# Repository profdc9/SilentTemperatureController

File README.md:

# Silent Temperature Controller

This is a heating temperature controller intended to minimize the vibrations caused by the heating element.  It uses kHz speed PWM modulated DC, rather than switching 50 or 60 cycle mains power, to power the heating elements.  For explosing holographic emulsions, the temperature must be stable and the vibrations must be minimized so that the sub-wavelength interference features are preserved.  By using high frequency PWM, the mechanical vibration or magnetostriction of the heating element coils is raised above a likely resonance frequency and therefore unlikely to cause significant vibrational movement.

The temperature controller can use up to three B3950 10k nominal resistance thermistors, or alternatively a LM335 temperature-based zener diode.  Reference thermistors may be added so that differential measurements can be taken to compensate for component temperature drift.  The controller supports up to four heating elements.  The DC power supply is up to 24 volts and 10 amps or so, with the limitation given by the trace width on the PCB.  If additional power bus wires are soldered in parallel with the traces, a higher current capacity is likely possible.  It is best to place the thermistors and heating elements in a vibration isolated, thermally insulated enclosure in which the hologram is exposed, with the enclosure being small enough so that the heaters can maintain a constant temperature throughout the volume.  A vibration-isolated platform may be achieved by placing a heavy cement slab or granite slab on partially inflated tires, and the granite slab may be made part of a thermally insulated enclosure using polystryrene slabs as walls.

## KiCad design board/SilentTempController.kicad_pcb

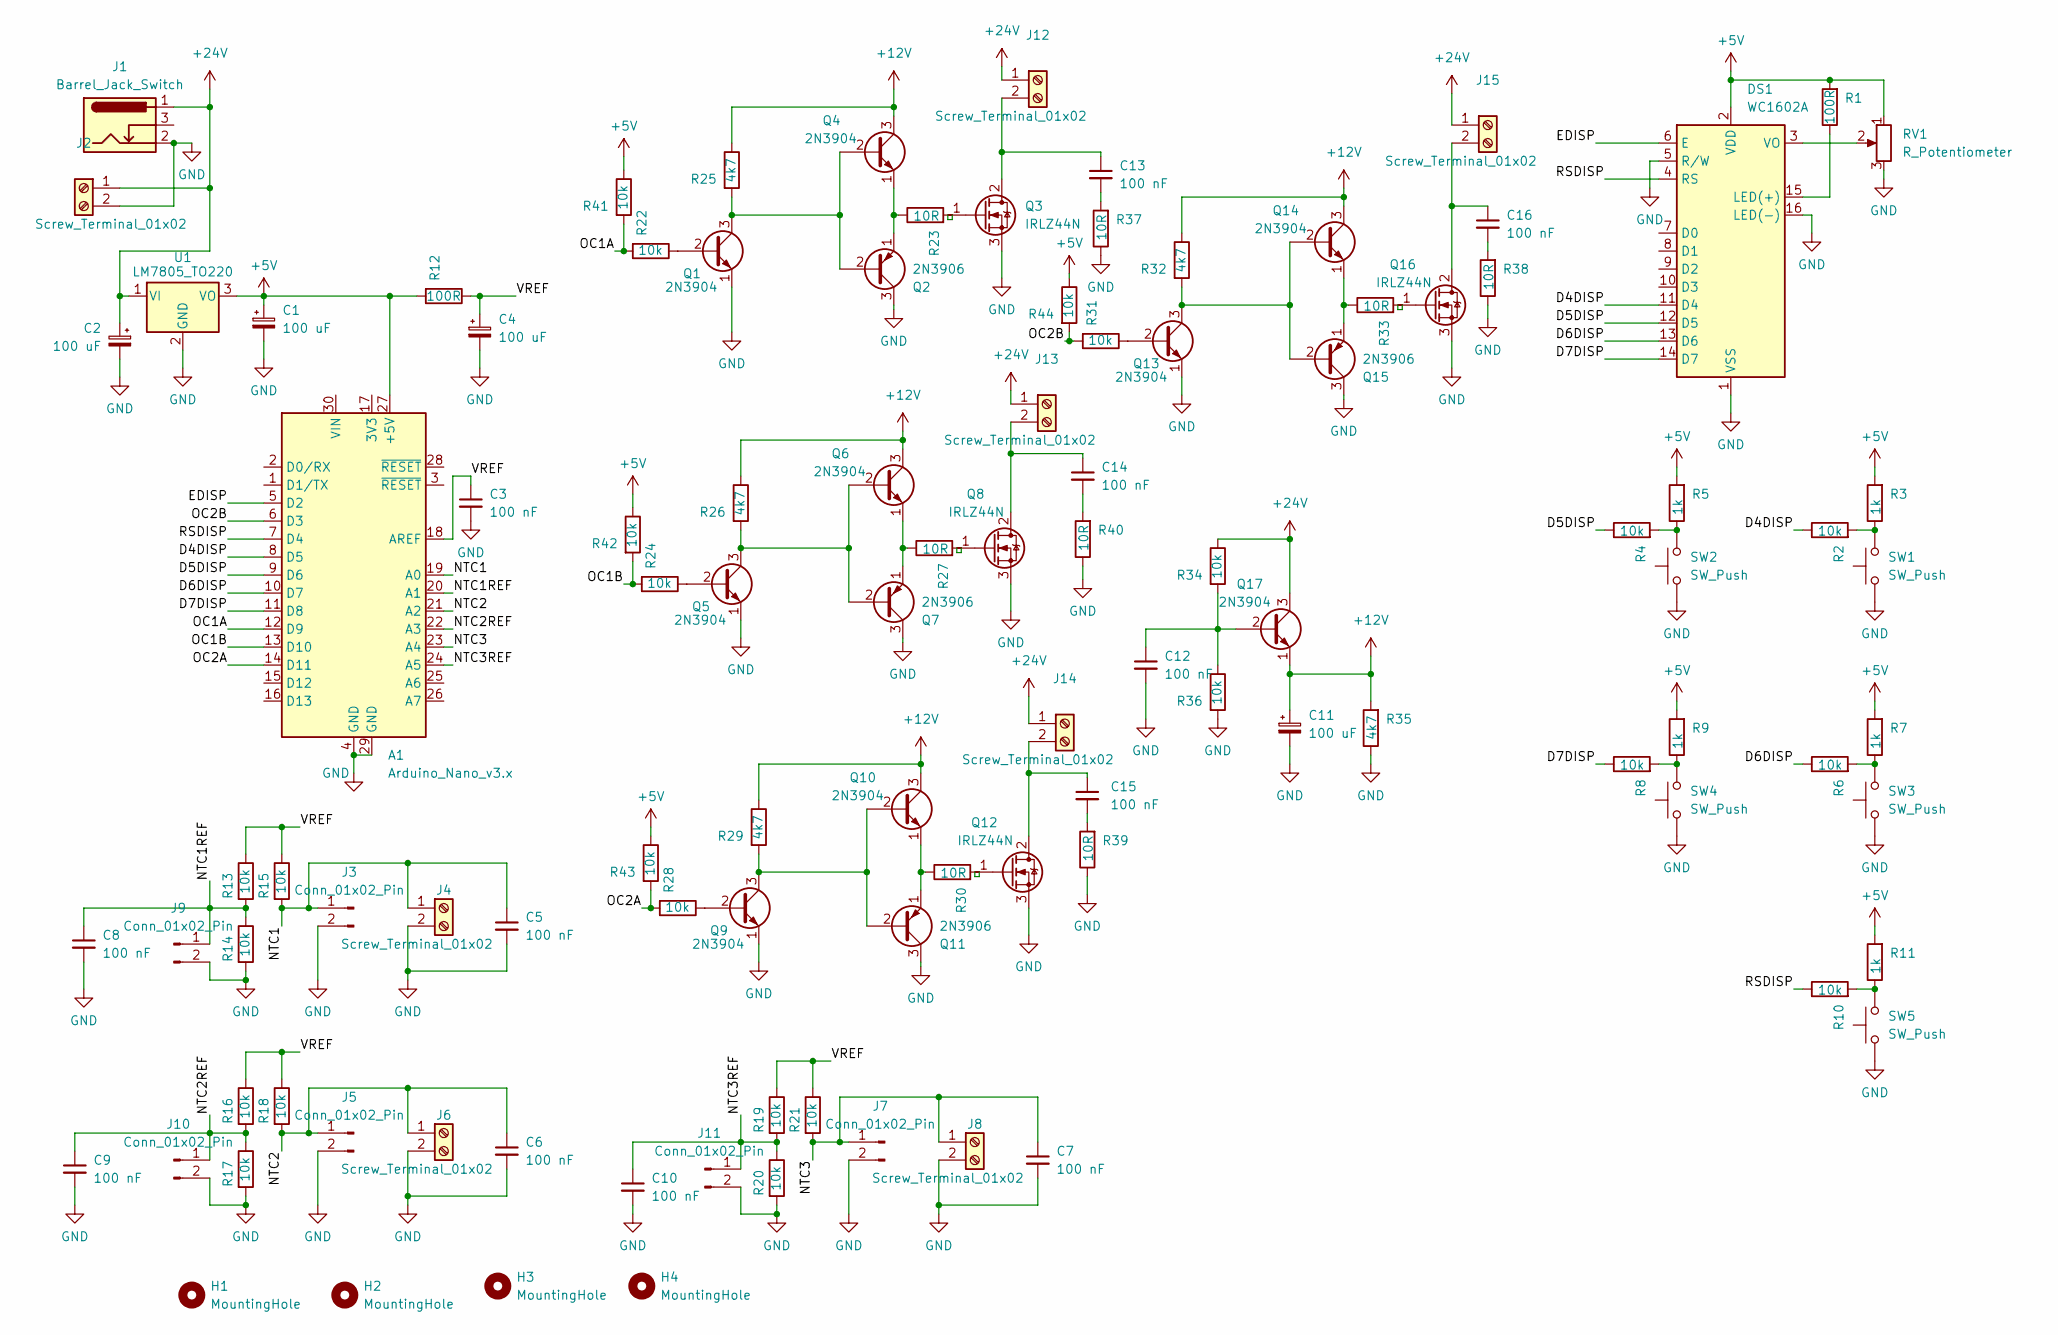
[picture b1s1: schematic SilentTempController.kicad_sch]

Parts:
A1: Arduino_Nano_v3.x; Arduino_Nano
C1, C2, C4, C11: 100 uF; CP_Radial_D7.5mm_P2.50mm
C3, C5, C6, C7, C8, C9, C10, C12, C13, C14, C15, C16: 100 nF; C_Disc_D5.0mm_W2.5mm_P5.00mm
DS1: WC1602A
H1, H2, H3, H4: MountingHole; MountingHole_3.2mm_M3
J1: Barrel_Jack_Switch; BarrelJack_Horizontal
J2, J4, J6, J8, J12, J13, J14, J15: Screw_Terminal_01x02; TerminalBlock_bornier-2_P5.08mm
J3, J5, J7, J9, J10, J11: Conn_01x02_Pin; PinHeader_1x02_P2.54mm_Vertical
Q1, Q4, Q5, Q6, Q9, Q10, Q13, Q14, Q17: 2N3904; TO-92_Inline_Wide
Q2, Q7, Q11, Q15: 2N3906; TO-92_Inline_Wide
Q3, Q8, Q12, Q16: IRLZ44N; TO-220-3_Vertical
R1, R12: 100R; R_Axial_DIN0207_L6.3mm_D2.5mm_P7.62mm_Horizontal
R2, R4, R6, R8, R10, R13, R14, R15, R16, R17, R18, R19, R20, R21, R22, R24, R28, R31, R34, R36, R41, R42, R43, R44: 10k; R_Axial_DIN0207_L6.3mm_D2.5mm_P7.62mm_Horizontal
R3, R5, R7, R9, R11: 1k; R_Axial_DIN0207_L6.3mm_D2.5mm_P7.62mm_Horizontal
R23, R27, R30, R37, R38, R39, R40: 10R; R_Axial_DIN0207_L6.3mm_D2.5mm_P7.62mm_Horizontal
R25, R26, R29, R32, R35: 4k7; R_Axial_DIN0207_L6.3mm_D2.5mm_P7.62mm_Horizontal
R33: 10R; R_Axial_DIN0207_L6.3mm_D2.5mm_P10.16mm_Horizontal
RV1: R_Potentiometer; Potentiometer_Bourns_3296W_Vertical
SW1, SW2, SW3, SW4, SW5: SW_Push; SW_PUSH_6mm
U1: LM7805_TO220; TO-220-3_Vertical

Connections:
+5V: A1.27 (+5V), C1.1, DS1.2 (VDD), R1.2, R3.2, R5.2, R7.2, R9.2, R11.2, R12.2, R41.1, R42.1, R43.1, R44.1, RV1.1, U1.3 (VO)
+12V: C11.1, Q4.3 (C), Q6.3 (C), Q10.3 (C), Q14.3 (C), Q17.1 (E), R25.1, R26.1, R29.1, R32.1, R35.2
+24V: C2.1, J1.1, J2.1, J12.1, J13.1, J14.1, J15.1, Q17.3 (C), R34.1, U1.1 (VI)
/D4DISP: A1.8 (D5), DS1.11 (D4), R2.1
/D5DISP: A1.9 (D6), DS1.12 (D5), R4.1
/D6DISP: A1.10 (D7), DS1.13 (D6), R6.1
/D7DISP: A1.11 (D8), DS1.14 (D7), R8.1
/EDISP: A1.5 (D2), DS1.6 (E)
/NTC1: A1.19 (A0), C5.1, J3.1, J4.1, R15.2
/NTC1REF: A1.20 (A1), C8.1, J9.1, R13.2, R14.1
/NTC2: A1.21 (A2), C6.1, J5.1, J6.1, R18.2
/NTC2REF: A1.22 (A3), C9.1, J10.1, R16.2, R17.1
/NTC3: A1.23 (A4), C7.1, J7.1, J8.1, R21.2
/NTC3REF: A1.24 (A5), C10.1, J11.1, R19.2, R20.1
/OC1A: A1.12 (D9), R22.2, R41.2
/OC1B: A1.13 (D10), R24.2, R42.2
/OC2A: A1.14 (D11), R28.2, R43.2
/OC2B: A1.6 (D3), R31.2, R44.2
/RSDISP: A1.7 (D4), DS1.4 (RS), R10.1
/VREF: A1.18 (AREF), C3.1, C4.1, R12.1, R13.1, R15.1, R16.1, R18.1, R19.1, R21.1
GND: A1.4 (GND), A1.29 (GND), C1.2, C2.2, C3.2, C4.2, C5.2, C6.2, C7.2, C8.2, C9.2, C10.2, C11.2, C12.2, DS1.1 (VSS), DS1.5 (R/W), DS1.16 (LED(-)), J1.2, J2.2, J3.2, J4.2, J5.2, J6.2, J7.2, J8.2, J9.2, J10.2, J11.2, Q1.1 (E), Q2.3 (C), Q3.3 (S), Q5.1 (E), Q7.3 (C), Q8.3 (S), Q9.1 (E), Q11.3 (C), Q12.3 (S), Q13.1 (E), Q15.3 (C), Q16.3 (S), R14.2, R17.2, R20.2, R35.1, R36.2, R37.1, R38.1, R39.1, R40.1, RV1.3, SW1.1, SW2.1, SW3.1, SW4.1, SW5.1, U1.2 (GND)
unnamed: C13.2, R37.2
unnamed: C14.2, R40.2
unnamed: C15.2, R39.2
unnamed: C16.2, R38.2
unnamed: DS1.15 (LED(+)), R1.1
unnamed: DS1.3 (VO), RV1.2
unnamed: C13.1, J12.2, Q3.2 (D)
unnamed: C14.1, J13.2, Q8.2 (D)
unnamed: C15.1, J14.2, Q12.2 (D)
unnamed: C16.1, J15.2, Q16.2 (D)
unnamed: Q1.2 (B), R22.1
unnamed: Q1.3 (C), Q2.2 (B), Q4.2 (B), R25.2
unnamed: Q2.1 (E), Q4.1 (E), R23.1
unnamed: Q3.1 (G), R23.2
unnamed: Q5.2 (B), R24.1
unnamed: Q5.3 (C), Q6.2 (B), Q7.2 (B), R26.2
unnamed: Q6.1 (E), Q7.1 (E), R27.1
unnamed: Q8.1 (G), R27.2
unnamed: Q9.2 (B), R28.1
unnamed: Q9.3 (C), Q10.2 (B), Q11.2 (B), R29.2
unnamed: Q10.1 (E), Q11.1 (E), R30.1
unnamed: Q12.1 (G), R30.2
unnamed: Q13.2 (B), R31.1
unnamed: Q13.3 (C), Q14.2 (B), Q15.2 (B), R32.2
unnamed: Q14.1 (E), Q15.1 (E), R33.1
unnamed: Q16.1 (G), R33.2
unnamed: C12.1, Q17.2 (B), R34.2, R36.1
unnamed: R2.2, R3.1, SW1.2
unnamed: R4.2, R5.1, SW2.2
unnamed: R6.2, R7.1, SW3.2
unnamed: R8.2, R9.1, SW4.2
unnamed: R10.2, R11.1, SW5.2

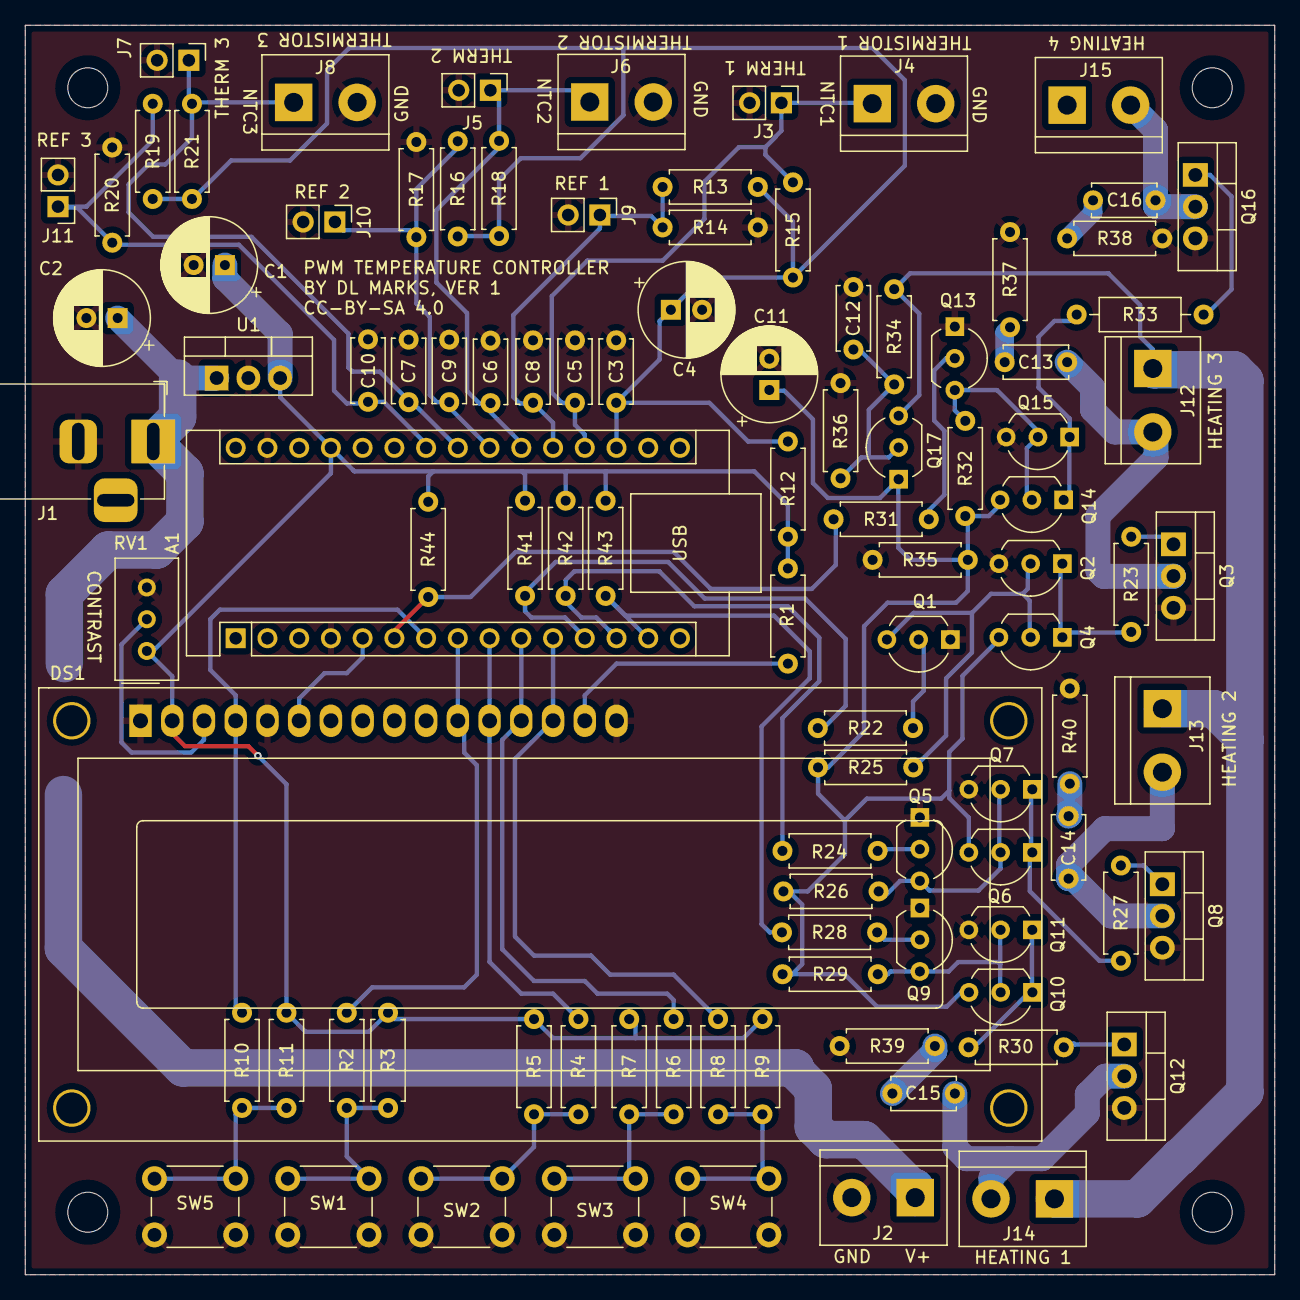
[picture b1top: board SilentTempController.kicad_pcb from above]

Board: 2 copper layers, 100.0 x 100.0 mm, 105 parts (0 on the bottom side), 53 nets.

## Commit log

2025-08-25 correct pic
2025-08-26 Added snubbers
2025-08-26 moved connectors
2025-08-30 improved snubbers
2025-08-31 Added on protection
2025-09-06 JLCPCB order

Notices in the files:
board/SilentTempController.kicad_pcb:
CC-BY-SA 4.0
